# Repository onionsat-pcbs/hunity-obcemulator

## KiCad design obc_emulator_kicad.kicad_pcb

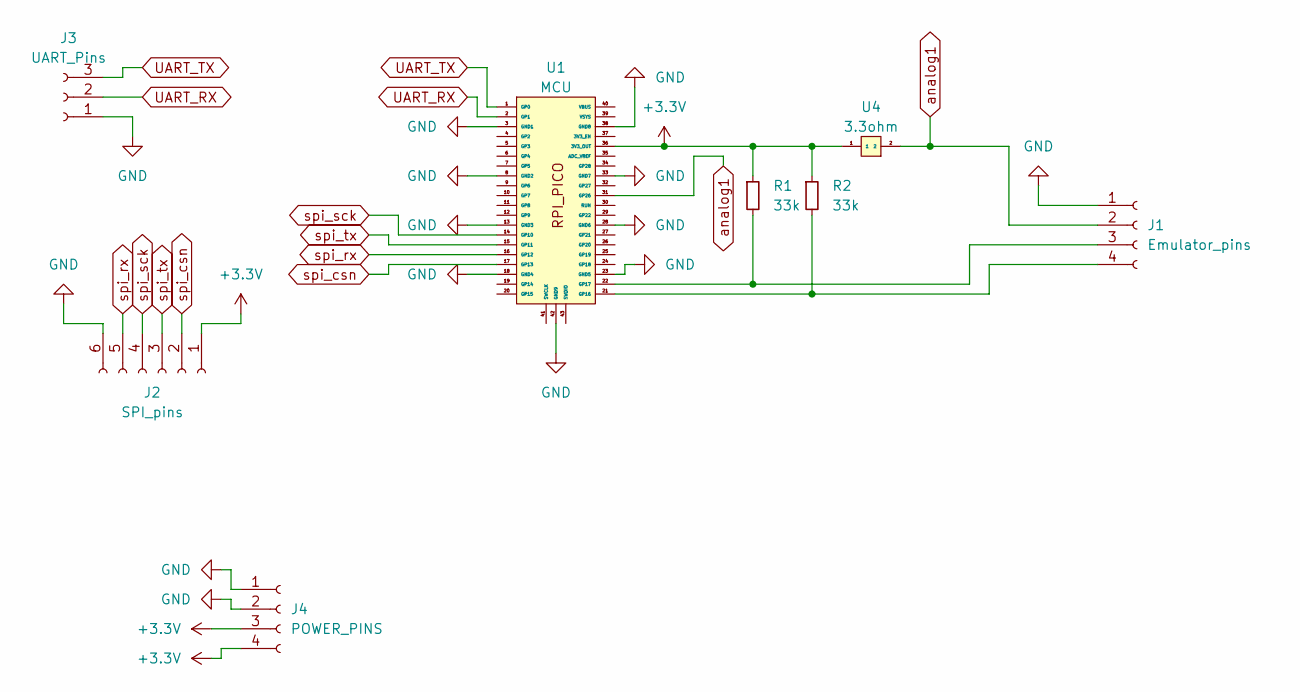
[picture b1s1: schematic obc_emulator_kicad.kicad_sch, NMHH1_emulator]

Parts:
J1: Emulator_pins; PinSocket_1x04_P2.54mm_Vertical
J2: SPI_pins; PinSocket_1x06_P2.54mm_Vertical
J3: UART_Pins; PinSocket_1x03_P2.54mm_Vertical
J4: POWER_PINS; PinSocket_1x04_P2.54mm_Vertical
R1, R2: 33k; R_0603_1608Metric_Pad0.98x0.95mm_HandSolder
U1: MCU; rpi_footprint
U4: 3.3ohm; 5W_3.3ohm

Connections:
+3.3V: J2.1, J4.3, J4.4, R1.1, R2.1, U1.36 (3V3_OUT), U4.1
GND: J1.1, J2.6, J3.1, J4.1, J4.2, U1.3 (GND1), U1.8 (GND2), U1.13 (GND3), U1.18 (GND4), U1.23 (GND5), U1.28 (GND6), U1.33 (GND7), U1.38 (GND8), U1.42 (GND9)
unnamed: J1.3, R1.2, U1.22 (GP17)
unnamed: J1.4, R2.2, U1.21 (GP16)
UART_RX: J3.2, U1.2 (GP1)
UART_TX: J3.3, U1.1 (GP0)
analog1: J1.2, U1.31 (GP26), U4.2
spi_csn: J2.2, U1.17 (GP13)
spi_rx: J2.5, U1.16 (GP12)
spi_sck: J2.4, U1.14 (GP10)
spi_tx: J2.3, U1.15 (GP11)

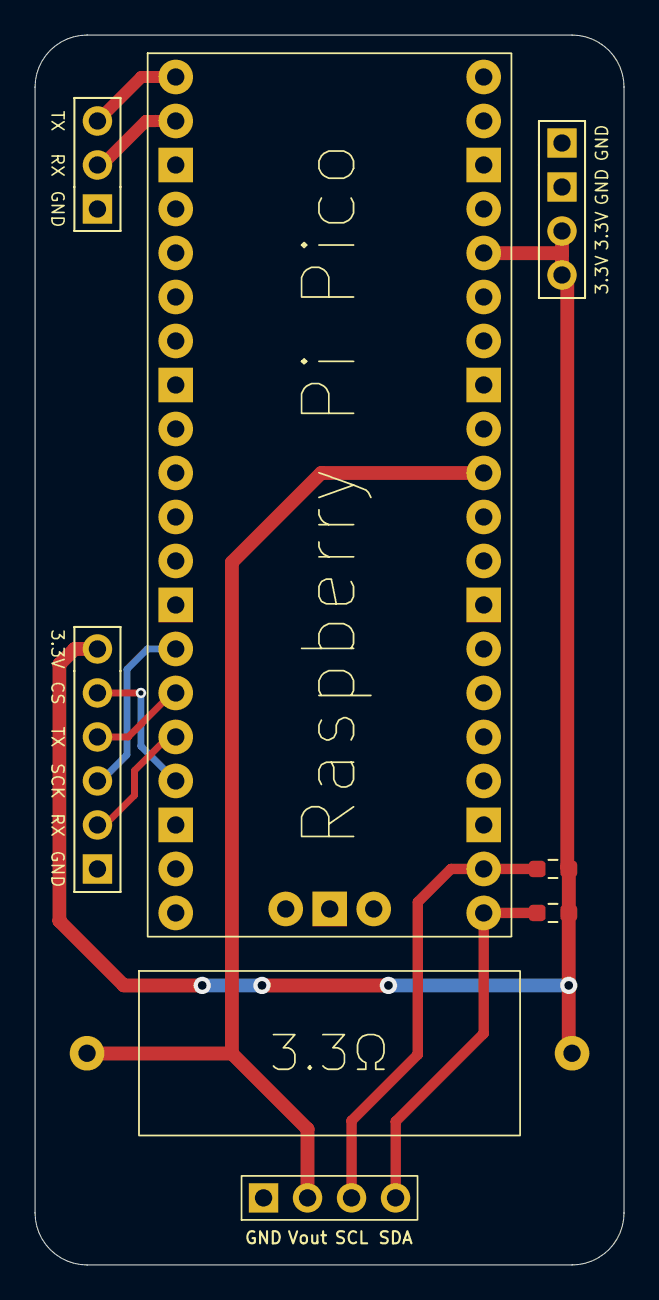
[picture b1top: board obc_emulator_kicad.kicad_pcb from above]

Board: 2 copper layers, 34.0 x 71.0 mm, 8 parts (0 on the bottom side), 11 nets.

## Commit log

2025-05-28 initila relase
2026-04-16 Puszi a pocira
